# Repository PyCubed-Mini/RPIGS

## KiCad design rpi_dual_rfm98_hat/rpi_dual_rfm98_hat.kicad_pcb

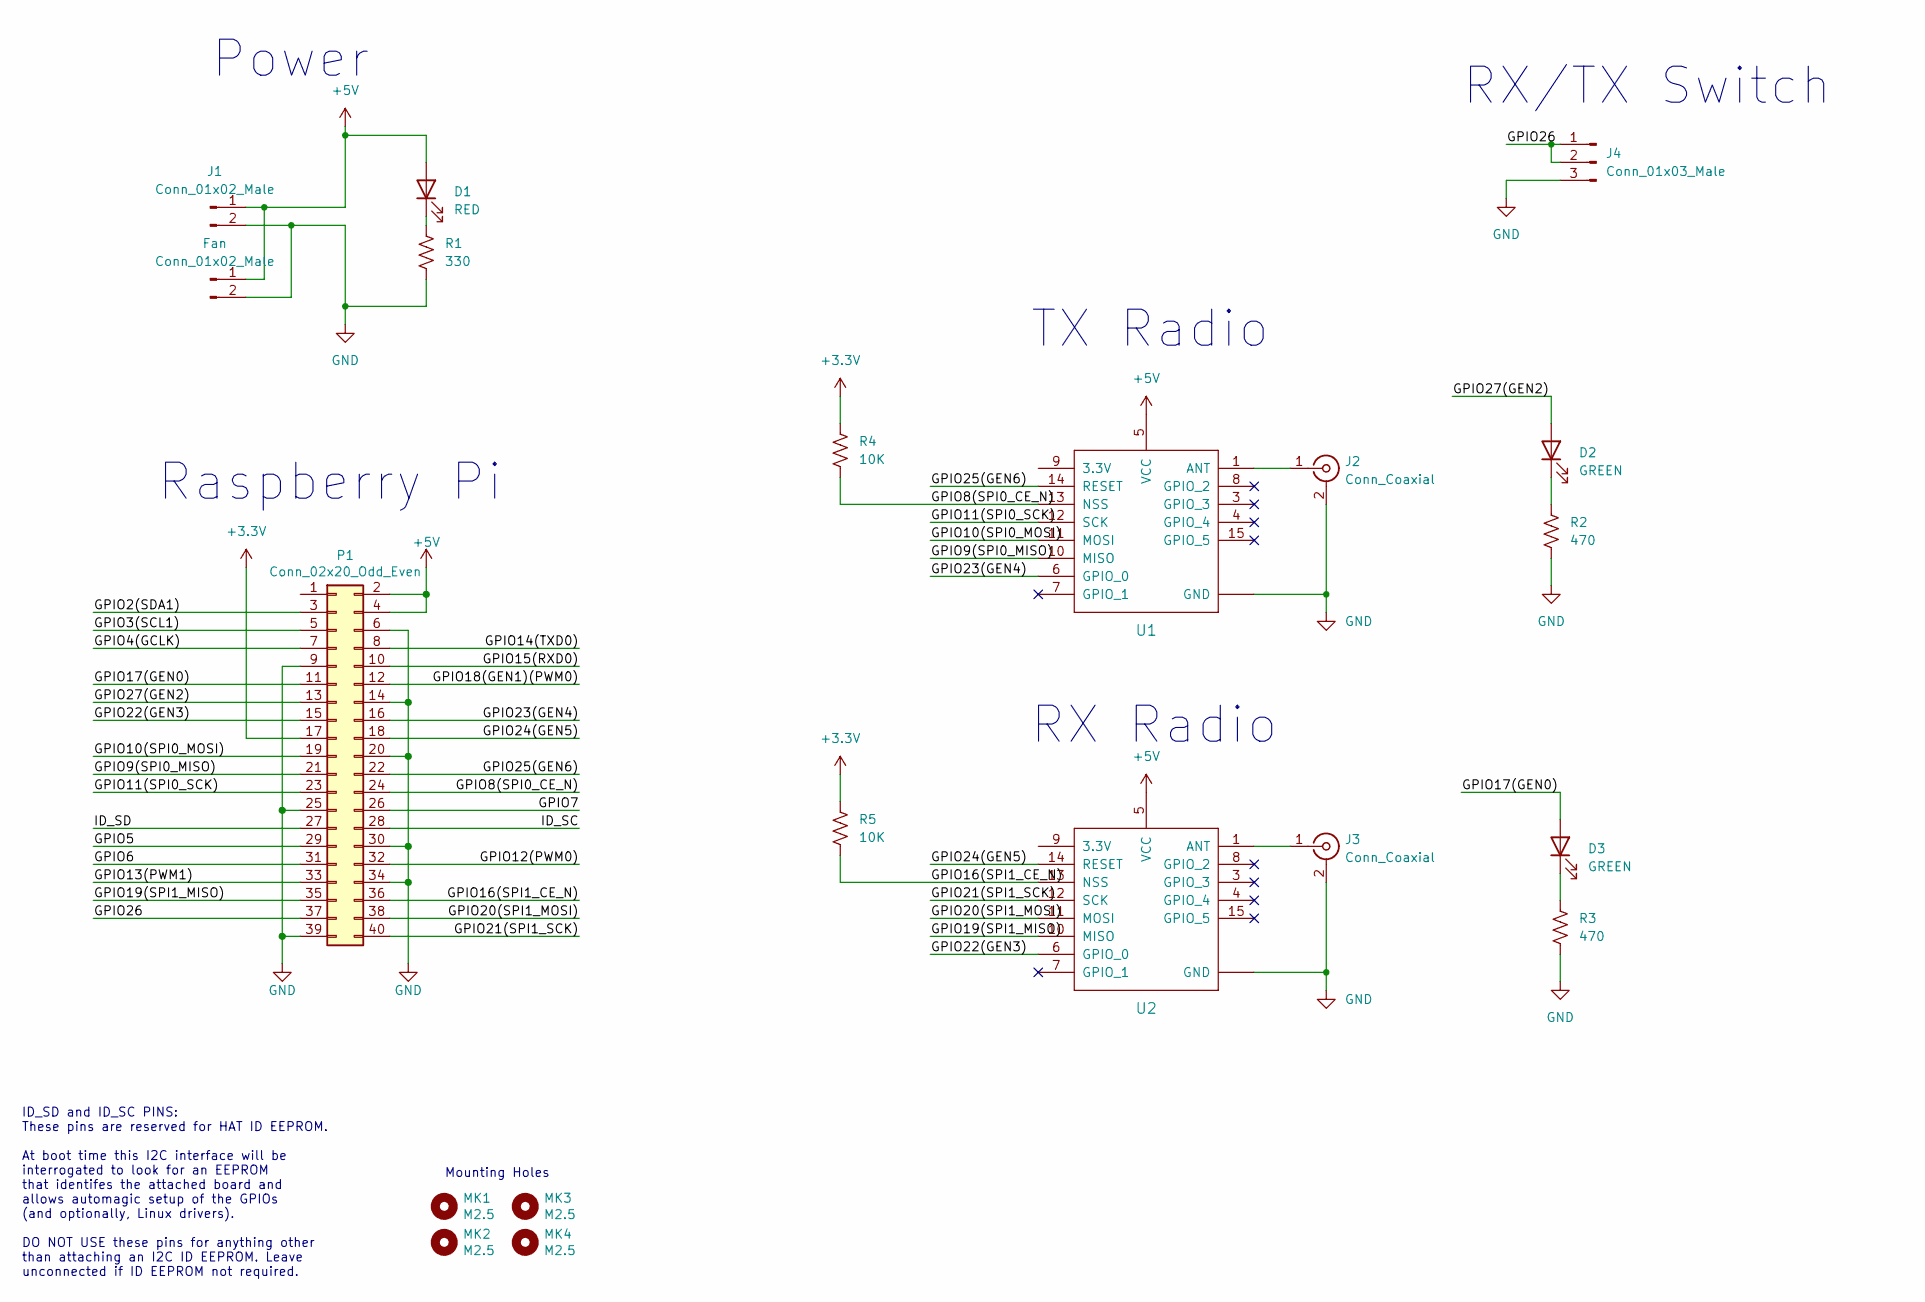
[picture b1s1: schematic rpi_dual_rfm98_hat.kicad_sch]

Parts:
D1: RED; LED_0603_1608Metric
D2, D3: GREEN; LED_0603_1608Metric
Fan: Conn_01x02_Male; PinHeader_1x02_P2.54mm_Vertical
J1: Conn_01x02_Male; JST_XH_B2B-XH-AM_1x02_P2.50mm_Vertical
J2, J3: Conn_Coaxial; SMA_Amphenol_132134-11_Vertical
J4: Conn_01x03_Male; JST_XH_B3B-XH-AM_1x03_P2.50mm_Vertical
MK1, MK2, MK3, MK4: M2.5; MountingHole_2.7mm_M2.5
P1: Conn_02x20_Odd_Even; PinSocket_2x20_P2.54mm_Vertical
R1: 330; R_0603_1608Metric
R2, R3: 470; R_0603_1608Metric
R4, R5: 10K; R_0603_1608Metric
U1, U2: RFM98PW-symbols; RFM95PW

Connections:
+3V3: P1.17, R4.1, R5.1
+5V: D1.2 (A), Fan.1, J1.1, P1.2, P1.4, U1.5 (VCC), U2.5 (VCC)
/GPIO2(SDA1): P1.3
/GPIO3(SCL1): P1.5
/GPIO4(GCLK): P1.7
/GPIO5: P1.29
/GPIO6: P1.31
/GPIO7: P1.26
/GPIO8(SPI0_CE_N): P1.24, R4.2, U1.13 (NSS)
/GPIO9(SPI0_MISO): P1.21, U1.10 (MISO)
/GPIO10(SPI0_MOSI): P1.19, U1.11 (MOSI)
/GPIO11(SPI0_SCK): P1.23, U1.12 (SCK)
/GPIO12(PWM0): P1.32
/GPIO13(PWM1): P1.33
/GPIO14(TXD0): P1.8
/GPIO15(RXD0): P1.10
/GPIO16(SPI1_CE_N): P1.36, R5.2, U2.13 (NSS)
/GPIO17(GEN0): D3.2 (A), P1.11
/GPIO18(GEN1)(PWM0): P1.12
/GPIO19(SPI1_MISO): P1.35, U2.10 (MISO)
/GPIO20(SPI1_MOSI): P1.38, U2.11 (MOSI)
/GPIO21(SPI1_SCK): P1.40, U2.12 (SCK)
/GPIO22(GEN3): P1.15, U2.6 (GPIO_0)
/GPIO23(GEN4): P1.16, U1.6 (GPIO_0)
/GPIO24(GEN5): P1.18, U2.14 (RESET)
/GPIO25(GEN6): P1.22, U1.14 (RESET)
/GPIO26: J4.1, J4.2, P1.37
/GPIO27(GEN2): D2.2 (A), P1.13
/ID_SC: P1.28
/ID_SD: P1.27
GND: Fan.2, J1.2, J2.2 (Ext), J3.2 (Ext), J4.3, P1.6, P1.9, P1.14, P1.20, P1.25, P1.30, P1.34, P1.39, R1.2, R2.2, R3.2, U1.2 (GND), U1.16 (GND), U1.17 (GND), U2.2 (GND), U2.16 (GND), U2.17 (GND)
unnamed: D1.1 (K), R1.1
unnamed: D2.1 (K), R2.1
unnamed: D3.1 (K), R3.1
unnamed: J2.1 (In), U1.1 (ANT)
unnamed: J3.1 (In), U2.1 (ANT)

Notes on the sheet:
RX Radio
RX/TX Switch
ID_SD and ID_SC PINS: These pins are reserved for HAT ID EEPROM. At boot time this I2C interface will be interrogated to look for an EEPROM that identifes the attached board and allows automagic setup of the GPIOs (and optionally, Linux drivers). DO NOT USE these pins for anything other than attach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
TX Radio
Raspberry Pi
Mounting Holes
Power

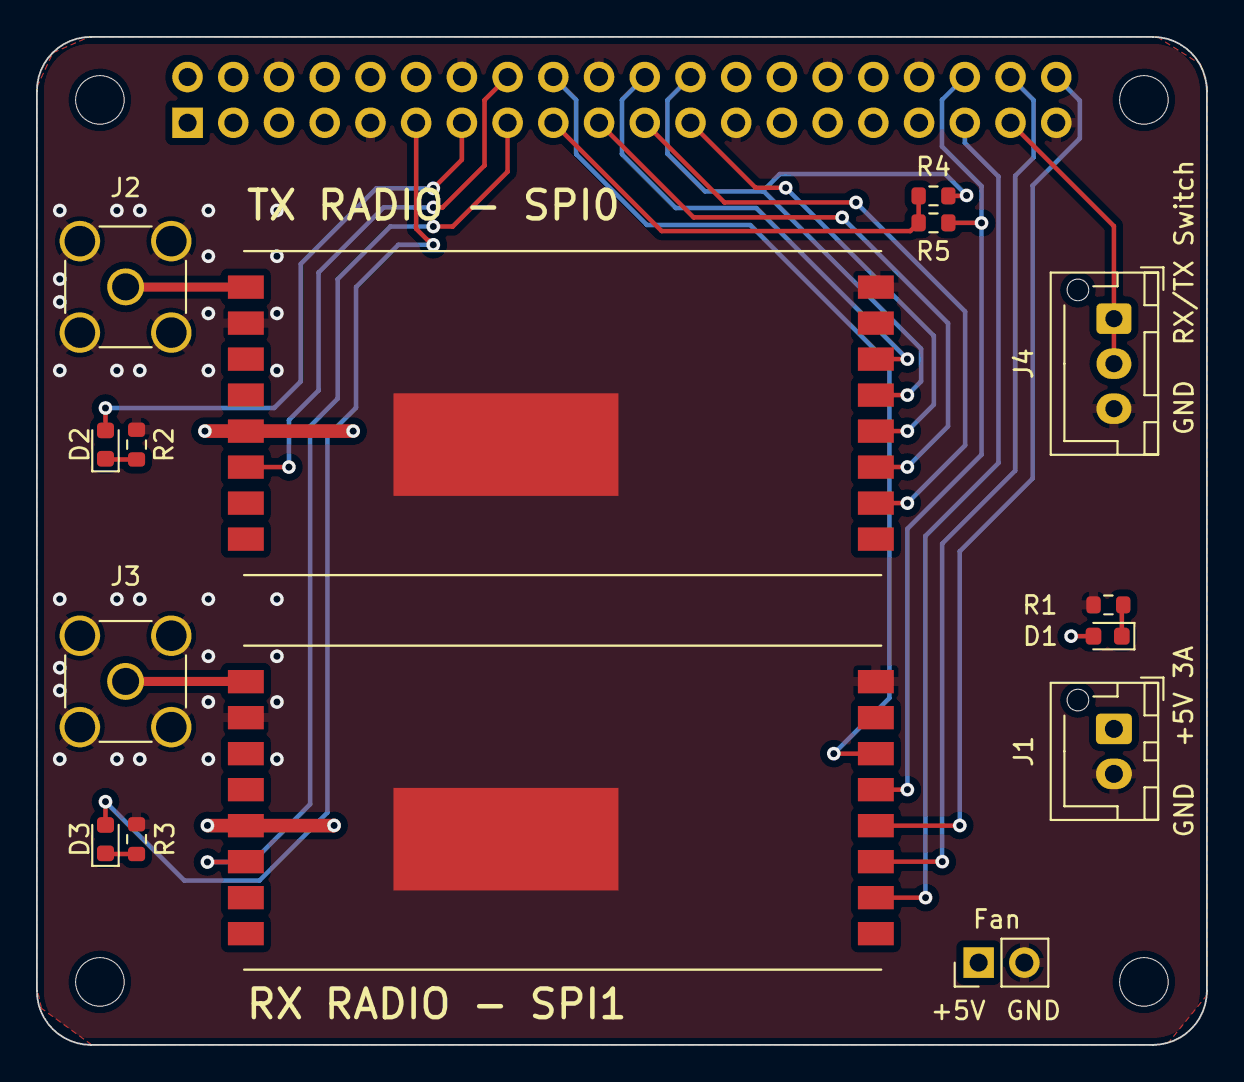
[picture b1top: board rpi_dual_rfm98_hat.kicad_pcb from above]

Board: 2 copper layers, 65.0 x 56.0 mm, 20 parts (1 on the bottom side), 23 nets.

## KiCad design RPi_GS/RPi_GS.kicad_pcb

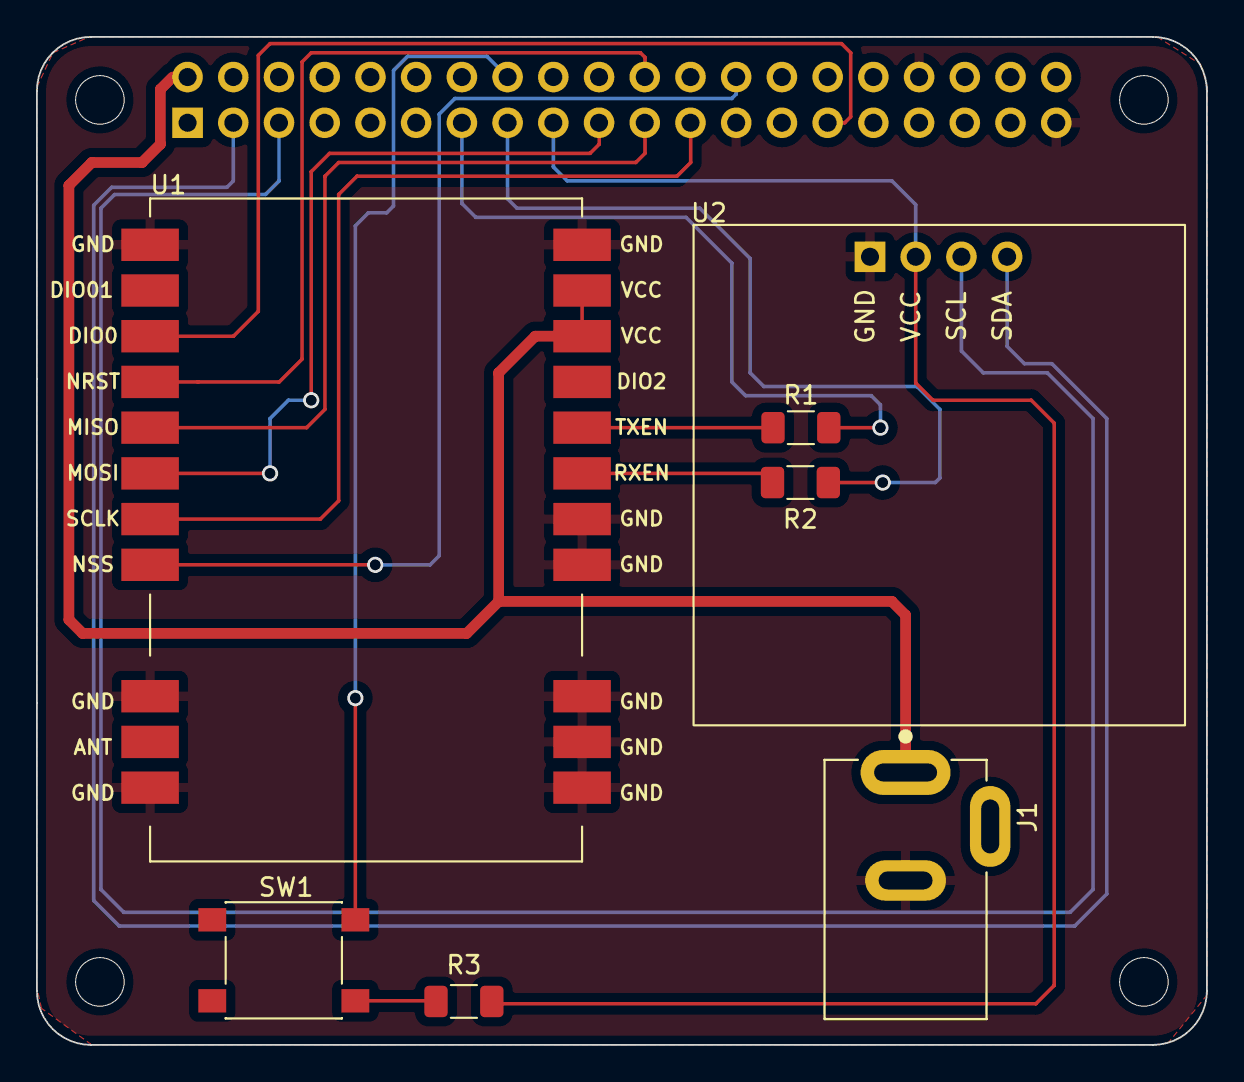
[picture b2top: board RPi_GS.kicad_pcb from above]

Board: 2 copper layers, 65.0 x 56.0 mm, 12 parts (1 on the bottom side), 17 nets.

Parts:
J1: PJ-202A; CUI_PJ-202A
MK1, MK2, MK3, MK4: M2.5; MountingHole_2.7mm_M2.5
P1: Conn_02x20_Odd_Even; PinSocket_2x20_P2.54mm_Vertical
R1, R2: 1k; R_1206_3216Metric_Pad1.30x1.75mm_HandSolder
R3: 10k; R_1206_3216Metric_Pad1.30x1.75mm_HandSolder
SW1: SW_Push_Open_Dual; SW_Push_1P1T_NO_6x6mm_H9.5mm
U1: E32400M30S; E32400M
U2: OLED

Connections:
+3V3: P1.1, P1.17, R3.1, U2.2 (VCC)
+5V: J1.1, P1.2, P1.4, U1.9 (VCC), U1.10 (VCC)
/GPIO2(SDA1): P1.3, U2.4 (SDA)
/GPIO3(SCL1): P1.5, U2.3 (SCL)
/GPIO5: P1.29, U1.20 (DIO0)
/GPIO7(SPI1_CE_N): P1.26, U1.25 (NSS)
/GPIO9(SPI0_MISO): P1.21, U1.22 (MISO)
/GPIO10(SPI0_MOSI): P1.19, U1.23 (MOSI)
/GPIO11(SPI0_SCK): P1.23, U1.24 (SCLK)
/GPIO22(GEN3): P1.15, R2.2
/GPIO23(GEN4): P1.16, SW1.2
/GPIO25(GEN6): P1.22, U1.21 (NRST)
/GPIO27(GEN2): P1.13, R1.2
GND: J1.2, P1.6, P1.9, P1.14, P1.20, P1.25, P1.30, P1.34, P1.39, U1.1 (GND), U1.2 (GND), U1.3 (GND), U1.4 (GND), U1.5 (GND), U1.11 (GND), U1.18 (GND), U1.26 (GND), U1.28 (GND), U2.1 (GND)
unnamed: R1.1, U1.7 (TXEN)
unnamed: R2.1, U1.6 (RXEN)
unnamed: R3.2, SW1.1

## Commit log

2022-09-20 Initial asyncio modifications
2022-09-20 change tasko to asyncio
2022-09-22 Added PCB files
2022-09-26 Added test button, changed to smd for whatever I could, added power planes
2022-11-30 different board name
2022-12-01 ready for review
2022-12-01 small fixes
2022-12-01 Fixed Outline Issue
2022-12-01 Re-mapped SPI1 CE pin
2022-12-01 don't track fp-info-cache
2022-12-01 newline
2022-12-01 ignore *auto_save*
2022-12-01 add CS pullups, ground under antenna connectors
2022-12-01 schematic changes aligning with previous commit
2022-12-02 Minor changes
2022-12-02 Added the fan connector
2022-12-02 thermal reliefs
